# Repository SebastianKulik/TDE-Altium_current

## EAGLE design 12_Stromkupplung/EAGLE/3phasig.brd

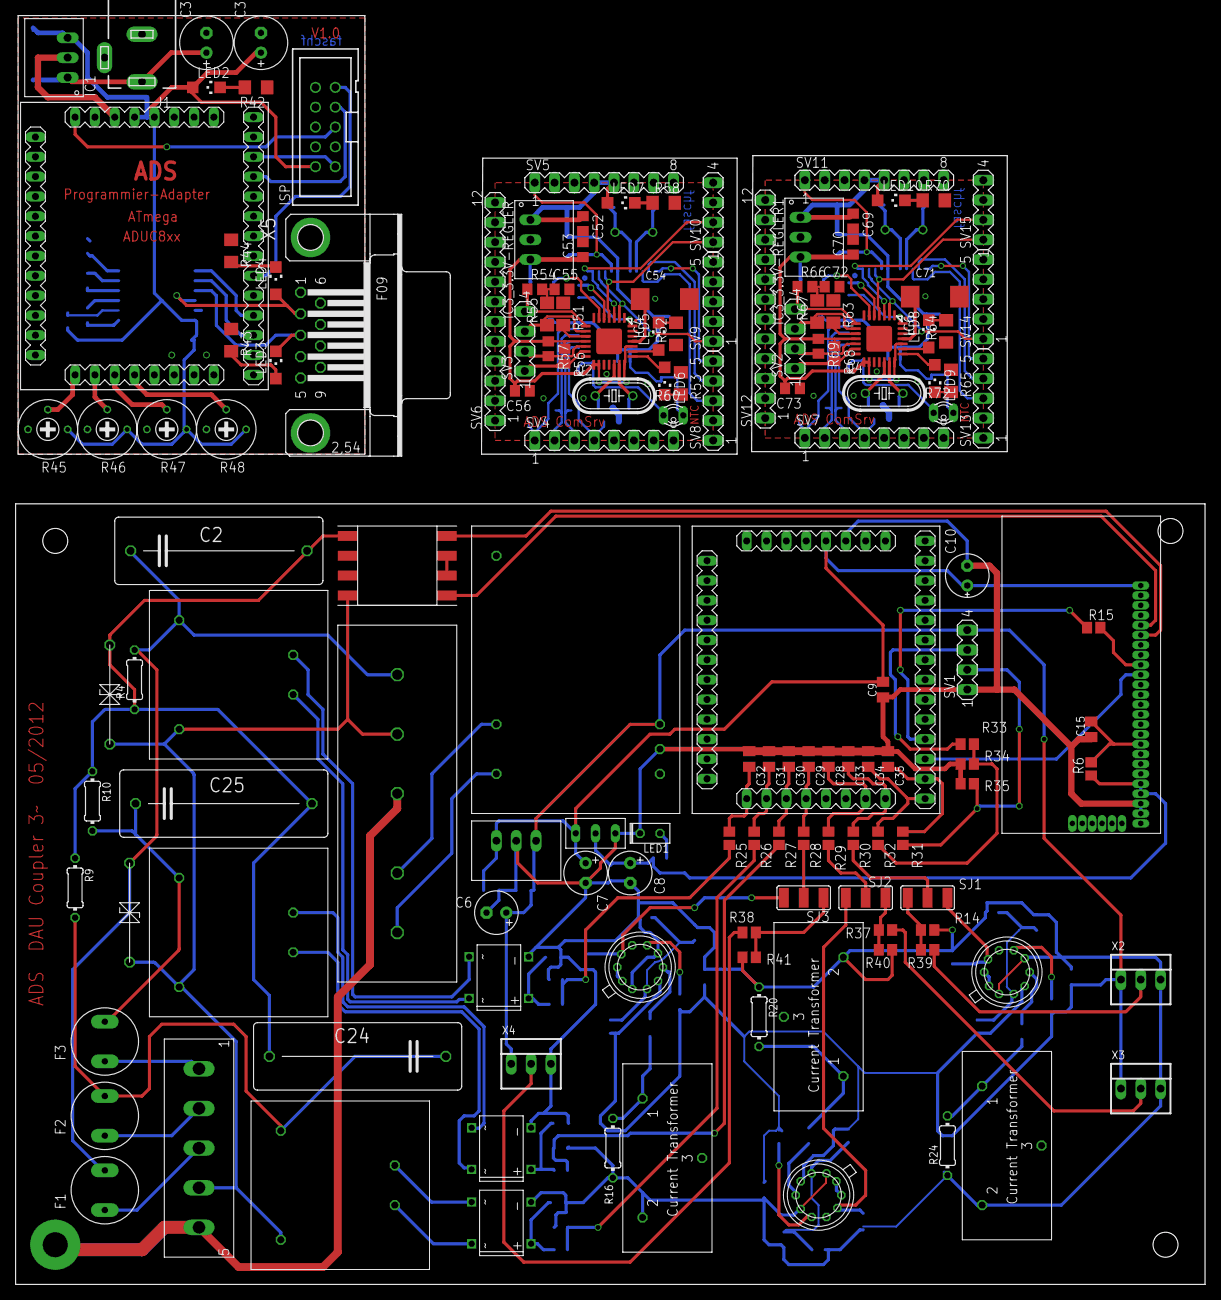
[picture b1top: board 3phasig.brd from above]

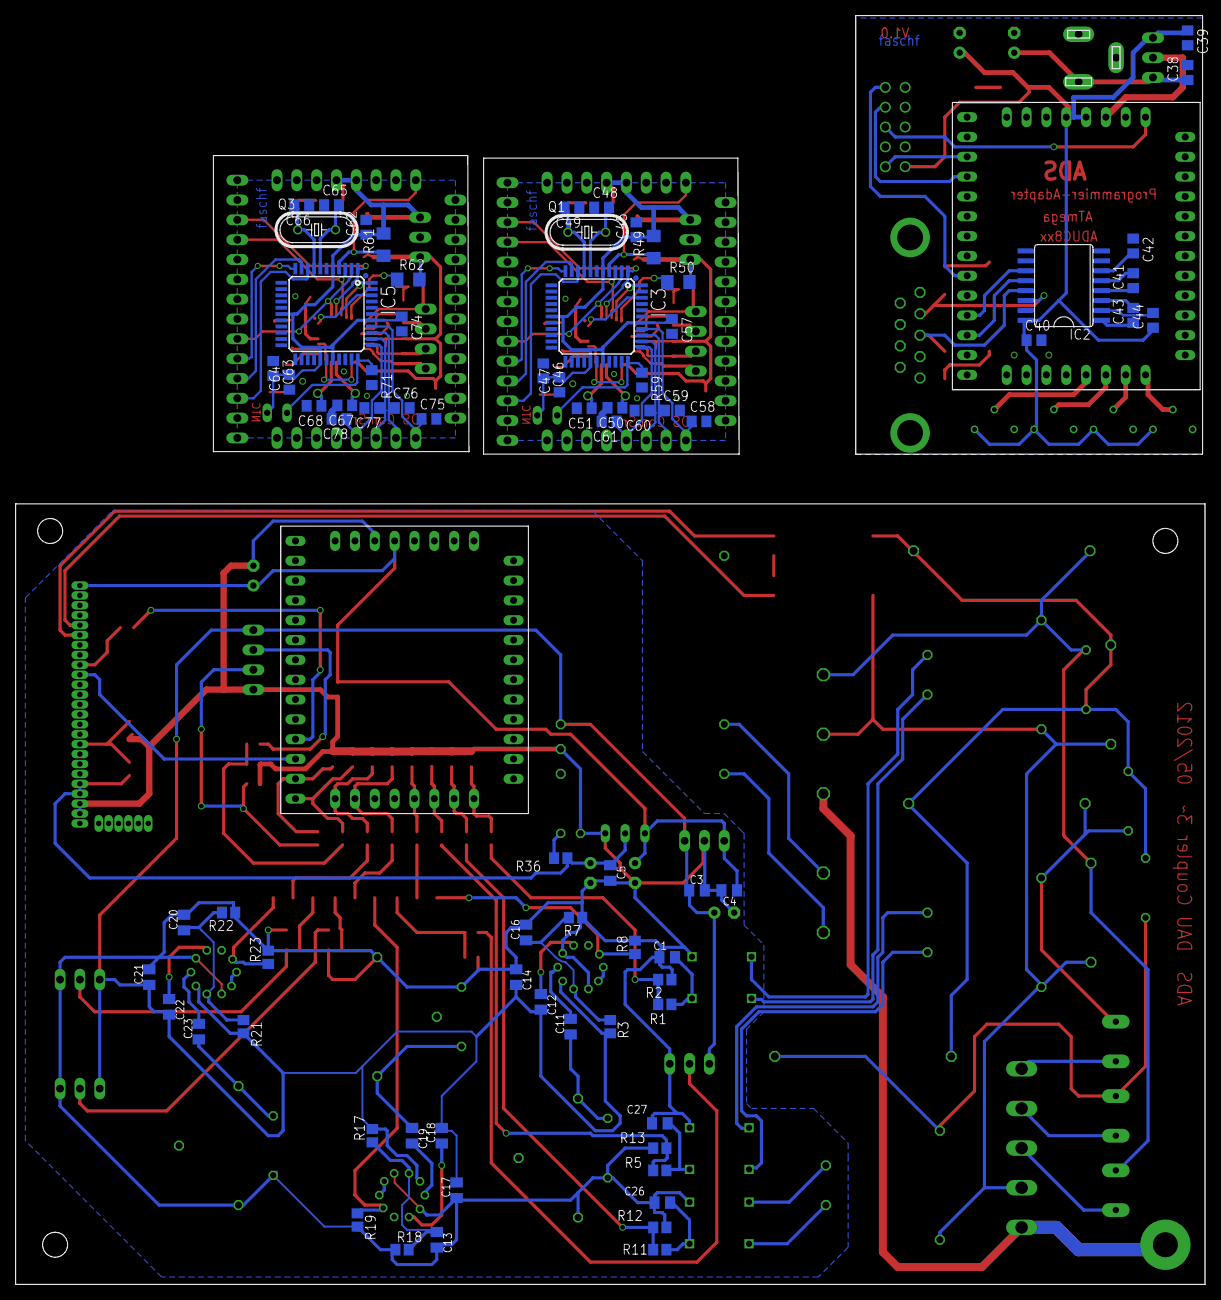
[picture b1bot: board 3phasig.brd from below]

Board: 2 copper layers, 152.4 x 162.5 mm, 222 parts (76 on the bottom side), 165 nets.

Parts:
AC1002_1: AC1010
C1, C11, C13, C14, C15, C16, C17, C19, C20, C21, C23, C26, C27: 1µ; C0805K
C2, C24, C25: 470n/270V; C225-087X268
C3, C4, C5, C9, C28, C29, C30, C31, C32, C33, C34, C35: 100n; C0805K
C6, C7, C8: 4,7µ; E2,5-6
C10: 4µ7; E2,5-6E
C12, C18, C22: 4µ7; C0805K
C36, C37: 10u; E2,5-7
C38, C39, C40, C41, C42, C43, C44, C45, C46, C47, C52, C53, C57, C62, C63, C64, C69, C70, C74: 100n; C0805
C48, C49, C50, C51, C65, C66, C67, C68: 22p; C0805
C54, C71: 10u; SMC_D
C55, C56, C58, C59, C60, C61, C72, C73, C75, C76, C77, C78: 10n; C0805
F1, F2, F3: T250mA/240V; TR5
IC1, IC3_3.3V-REGLER, IC3_3.3V-REGLER1: 78RECOM; RECOM_3POL
IC2: MAX3232CWE; SO16L
IC3, IC5: MEGA32-A; TQFP44
IC4, IC6: ENC28J60QFN28_LONG_28; QFN28_LONG_ERRLES
ISP: 2510-; PAK100/2500-10
J1: DCJ0202
LED1: LED2X5
LED2, LED3, LED4, LED5, LED6, LED7, LED8, LED9, LED10: CHIPLED_1206
P6KE300CA: P6KE300CA; TSV
Q1, Q3: 16MHz; HC49/S
Q2, Q4: 25MHz; HC49/S
R1, R5, R11: 82k; R0805
R2, R12, R13: 33k; R0805
R3, R17, R21: 22k; R0805
R4, R9, R10: 470k; 0204/7
R6: 1M; R0805
R7, R18, R22, R59, R71: 10k; R0805
R8, R19, R23: 4k7; R0805
R14, R40, R41: 220R/33k; R0805
R15, R36: 330R; R0805
R16, R20, R24: 68R; 0204/7
R25, R26, R27, R28, R29, R30, R31, R32: 10R; R0805
R33: 680k; R0805
R34: 470k; R0805
R35: 220R; R0805
R37, R38, R39: 0/82k; R0805
R42, R52, R53, R58, R64, R65, R70: 220R; R1206
R43, R44: 1k2; R1206
R45, R46, R47, R48: 100k; RTRIM3339P
R49, R50, R61, R62: 10k; R1206
R51, R63: 2k2; R1206
R54, R56, R57, R66, R68, R69: 51R; R0805
R55, R67: 51R; R1206
R60, R72: P640
SJ1, SJ2, SJ3: SJ_2W
SV1, SV2, SV3, SV10, SV15: MA04-1
SV4, SV5, SV7, SV11: MA08-1
SV6, SV12: MA12-1
SV8, SV9, SV13, SV14: MA05-1
TSV2: TSV
U$1: RECOM_RAC04_12SA; RAC04_12SA
U$2, U$16, U$18: SICHERHEITSTRAFO; TRAFO_0,35VA
U$3: ADUC831_MINIMUM; ADUC_MINIMUM
U$4: MODEMSTECKER; MODEM_FUSS
U$5: PLC_UEBERTRAGER_V2; PLC-UEBERTRAGER_V2
U$6: MEGA32_COMSERVER; ADUC_MINIMUM
U$7, U$14: AC1010
U$8, U$17, U$19: RECTIFIER
U$10: RECOM_785_05; RECOM785X
U$11: TS1084_HOCH
U$12, U$13, U$15: AD536; TO100_10PIN
U$20: NETZFILTER_05_A; NETZFILTER
X1: CONNECTO_5_POL; CONNECTOR_5_POL
X2, X3, X4: 22-23-2031
X5: F09HP

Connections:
1_TD+: IC4.13, R56.2, SV3.1
1_TD+1: IC6.13, R68.2, SV2.1
2_TD-: IC4.12, R57.2, SV3.2
2_TD-1: IC6.12, R69.2, SV2.2
3_RD+: IC4.9, R55.1, SV3.3
3_RD+1: IC6.9, R67.1, SV2.3
6_RD-: IC4.8, R54.1, SV3.4
6_RD-1: IC6.8, R66.1, SV2.4
+3V3: C5.1, C8.+, R6.1, R36.1, U$4.P$4, U$4.P$5, U$11.OUT
+5V: C4.1, C7.+, C9.2, C10.+, U$3.VCC, U$4.P$25, U$10.VOUT, U$11.IN
+12V: C3.1, C6.+, C12.2, C14.2, C17.2, C18.2, C21.1, C22.2, R3.2, R17.2, R21.2, SV1.4, U$1.+VO, U$10.VIN, U$12.3, U$13.3, U$15.3, X2.1, X3.1, X4.1
ADC0: C32.1, R25.2, U$3.ADC0
ADC1: C31.1, R26.2, U$3.ADC1
ADC2: C30.1, R27.2, U$3.ADC2
ADC3: C29.1, R28.2, U$3.ADC3
ADC4: C28.1, R29.2, U$3.ADC4
ADC5: C33.1, R30.2, U$3.ADC5
ADC6: C58.1, IC3.37, SV4.1
ADC7: C59.1, IC3.36, SV4.2
ADC8: C60.1, IC3.35, SV4.3
ADC9: C61.1, IC3.34, SV4.4
ADC10: C75.1, IC5.37, SV7.1
ADC11: C76.1, IC5.36, SV7.2
ADC12: C77.1, IC5.35, SV7.3
ADC13: C78.1, IC5.34, SV7.4
GND: AC1002_1.P$2, C1.2, C3.2, C4.2, C5.2, C6.-, C7.-, C8.-, C9.1, C10.-, C13.2, C14.1, C15.1, C16.2, C17.1, C20.2, C21.2, C26.2, C27.2, C28.2, C29.2, C30.2, C31.2, C32.2, C33.2, C34.2, C35.2, LED1.K, R2.1, R7.1, R8.2, R12.1, R13.1, R14.1, R16.1, R18.1, R19.2, R20.1, R22.1, R23.2, R24.1, R34.1, R35.1, R40.1, R41.1, SV1.1, U$1.GND, U$3.GND, U$4.P$2, U$4.P$3, U$7.P$2, U$8.-, U$10.GND, U$11.GND, U$12.1, U$12.5, U$13.1, U$13.5, U$14.P$2, U$15.1, U$15.5, U$17.-, U$19.-, X2.3, X3.3, X4.3
GND1: C36.-, C37.-, C38.2, C39.2, C40.2, C42.1, IC1.2, IC2.8, IC2.10, IC2.15, ISP.6, ISP.10, J1.2, J1.3, R42.1, R43.1, R44.1, R45.3, R46.3, R47.3, R48.3, U$6.GND, U$6.GND2, U$6.GND3, X5.5
GND2: C45.2, C46.1, C47.1, C48.1, C49.1, C50.2, C51.2, C52.2, C53.2, C54.-, C55.2, C56.1, C57.2, C58.2, C59.2, C60.2, C61.2, IC3.6, IC3.18, IC3.28, IC3.30, IC3.31, IC3.32, IC3.39, IC3_3.3V-REGLER.2, IC4.7, IC4.14, IC4.17, IC4.18, IC4.26, R51.1, R52.1, R53.1, R58.2, R59.2, SV5.2, SV5.3, SV5.6
GND3: C62.2, C63.1, C64.1, C65.1, C66.1, C67.2, C68.2, C69.2, C70.2, C71.-, C72.2, C73.1, C74.2, C75.2, C76.2, C77.2, C78.2, IC3_3.3V-REGLER1.2, IC5.6, IC5.18, IC5.28, IC5.30, IC5.31, IC5.32, IC5.39, IC6.7, IC6.14, IC6.17, IC6.18, IC6.26, R63.1, R64.1, R65.1, R70.2, R71.2, SV11.2, SV11.3, SV11.6
I1: R28.1, SJ3.2
I1INTERN: R8.1, SJ3.3, U$13.8
I2: R29.1, SJ2.2
I2INTERN: R19.1, SJ2.3, U$12.8
I3: R30.1, SJ1.2
I3INTERN: R23.1, SJ1.3, U$15.8
INT0: IC3.11, SV8.5
INT1: IC5.11, SV13.5
L1: C2.1, F1.2, P6KE300CA.P$1, R4.2, U$2.L, U$20.L
L2: C24.1, F2.2, R9.2, U$16.L
L3: C25.1, F3.2, R10.2, U$18.L
MISO: IC3.2, IC4.2, SV9.1
MISO1: IC5.2, IC6.2, SV14.1
MOSI: IC3.1, IC4.3, SV10.2
MOSI1: IC5.1, IC6.3, SV15.2
N: P6KE300CA.P$2, TSV2.P$2, U$2.N, U$5.8N, U$16.N, U$18.N, U$20.N, X1.P$4
unnamed: R15.2, U$4.P$17
unnamed: AC1002_1.P$1, C11.1, R16.2
unnamed: C11.2, U$13.4
unnamed: U$2.OUT1, U$8.~1
unnamed: U$4.P$20, U$5.1LINE1
unnamed: U$13.9, U$13.10
unnamed: C1.1, R1.2, U$8.+
unnamed: C35.1, R31.2, U$3.ADC7
unnamed: U$2.OUT2, U$8.~2
unnamed: C26.1, R11.2, U$17.+
unnamed: U$16.OUT1, U$17.~1
unnamed: U$16.OUT2, U$17.~2
unnamed: U$4.P$21, U$5.4LINE2
unnamed: R15.1, U$3.TXD
unnamed: U$3.RXD, U$4.P$16
unnamed: U$1.L, U$20.L'
unnamed: C16.1, R3.1, R7.2, U$13.2
unnamed: C36.+, C38.1, IC1.1, J1.1
unnamed: LED1.A, R36.2
unnamed: C15.2, R6.2, U$4.P$9
unnamed: C12.1, U$13.6
unnamed: C19.1, R20.2, U$7.P$1
unnamed: C19.2, U$12.4
unnamed: U$12.9, U$12.10
unnamed: C34.1, R32.2, U$3.ADC6
unnamed: C2.2, C24.2, C25.2, R4.1, R9.1, R10.1, TSV2.P$1, U$5.L5
unnamed: C13.1, R17.1, R18.2, U$12.2
unnamed: ISP.1, U$6.MOSI
unnamed: C18.1, U$12.6
unnamed: C23.1, R24.2, U$14.P$1
unnamed: C23.2, U$15.4
unnamed: U$15.9, U$15.10
unnamed: U$5.2, U$5.3
unnamed: C27.1, R5.2, U$19.+
unnamed: U$18.OUT1, U$19.~1
unnamed: U$18.OUT2, U$19.~2
unnamed: R33.2, SV1.3
unnamed: C20.1, R21.1, R22.2, U$15.2
unnamed: ISP.5, U$6.P24
unnamed: C22.1, U$15.6
unnamed: U$1.N, U$20.N'
unnamed: R37.2, R40.2, SJ2.1
unnamed: R37.1, X3.2
unnamed: R14.2, R39.2, SJ1.1
unnamed: F1.1, X1.P$3
unnamed: F2.1, X1.P$2
unnamed: F3.1, X1.P$1
unnamed: R32.1, R33.1, R34.2
unnamed: R31.1, R35.2, SV1.2
unnamed: R39.1, X2.2
unnamed: R38.2, R41.2, SJ3.1
unnamed: R38.1, X4.2
unnamed: ISP.7, U$6.SCLOCK
unnamed: ISP.9, U$6.MISO
unnamed: IC2.12, U$6.RXD
unnamed: IC2.11, U$6.TXD
unnamed: C44.2, IC2.2
unnamed: C42.2, IC2.6
unnamed: C43.1, IC2.1
unnamed: C43.2, IC2.3
unnamed: C41.1, IC2.4
unnamed: C41.2, IC2.5
unnamed: IC2.14, LED4.A, X5.2
unnamed: LED2.C, R42.2
unnamed: IC2.13, LED3.C, X5.3
unnamed: LED3.A, R43.2
unnamed: LED4.C, R44.2
unnamed: R45.2, U$6.ADC0
unnamed: R46.2, U$6.ADC1
unnamed: R47.2, U$6.ADC2
unnamed: R48.2, U$6.ADC3
unnamed: C49.2, IC3.8, Q1.1
unnamed: C48.2, IC3.7, Q1.2
unnamed: C50.1, IC4.19, Q2.1
unnamed: C51.1, IC4.20, Q2.2
unnamed: C54.+, IC4.25
unnamed: IC3.42, IC4.28
unnamed: IC4.6, R50.1
unnamed: IC4.10, R51.2
unnamed: LED5.C, R52.2
unnamed: IC4.23, LED5.A
unnamed: IC4.22, LED6.A
unnamed: LED6.C, R53.2
unnamed: C55.1, R54.2, R55.2
unnamed: LED7.C, R58.1
unnamed: IC3.33, R59.1, R60.1
unnamed: C66.2, IC5.8, Q3.1
unnamed: C65.2, IC5.7, Q3.2
unnamed: C67.1, IC6.19, Q4.1
unnamed: C68.1, IC6.20, Q4.2
unnamed: C71.+, IC6.25
unnamed: IC5.42, IC6.28
unnamed: IC6.6, R62.1
unnamed: IC6.10, R63.2
unnamed: LED8.C, R64.2
unnamed: IC6.23, LED8.A
unnamed: IC6.22, LED9.A
unnamed: LED9.C, R65.2
unnamed: C72.1, R66.2, R67.2
unnamed: LED10.C, R70.1
unnamed: IC5.33, R71.1, R72.1
PE: U$20.PE, X1.P$5
RESET: IC3.4, R49.1, SV5.1
RESET1: IC5.4, R61.1, SV11.1
RXD: IC3.9, SV8.3
RXD1: IC5.9, SV13.3
SCK: IC3.3, IC4.4, SV10.1
SCK1: IC5.3, IC6.4, SV15.1
SS: IC3.44, IC4.5
SS1: IC5.44, IC6.5
TXD: IC3.10, SV8.4
TXD1: IC5.10, SV13.4
U1: R1.1, R2.2, R25.1
U2: R11.1, R12.2, R26.1
U3: R5.1, R13.2, R27.1
VCC: C37.+, C39.1, C40.1, C44.1, IC1.3, IC2.16, ISP.2, LED2.A, R45.1, R46.1, R47.1, R48.1, U$6.VCC, U$6.VCC1
VCC_3V: C53.1, C56.2, IC3_3.3V-REGLER.3, IC4.11, IC4.15, IC4.16, IC4.21, IC4.24, R50.2, R56.1, R57.1
VCC_3V1: C70.1, C73.2, IC3_3.3V-REGLER1.3, IC6.11, IC6.15, IC6.16, IC6.21, IC6.24, R62.2, R68.1, R69.1
VCC_5V: C45.1, C46.2, C47.2, C52.1, C57.1, IC3.5, IC3.17, IC3.27, IC3.29, IC3.38, IC3_3.3V-REGLER.1, LED7.A, R49.2, R60.2, SV5.4, SV5.5
VCC_5V1: C62.1, C63.2, C64.2, C69.1, C74.1, IC3_3.3V-REGLER1.1, IC5.5, IC5.17, IC5.27, IC5.29, IC5.38, LED10.A, R61.2, R72.2, SV11.4, SV11.5

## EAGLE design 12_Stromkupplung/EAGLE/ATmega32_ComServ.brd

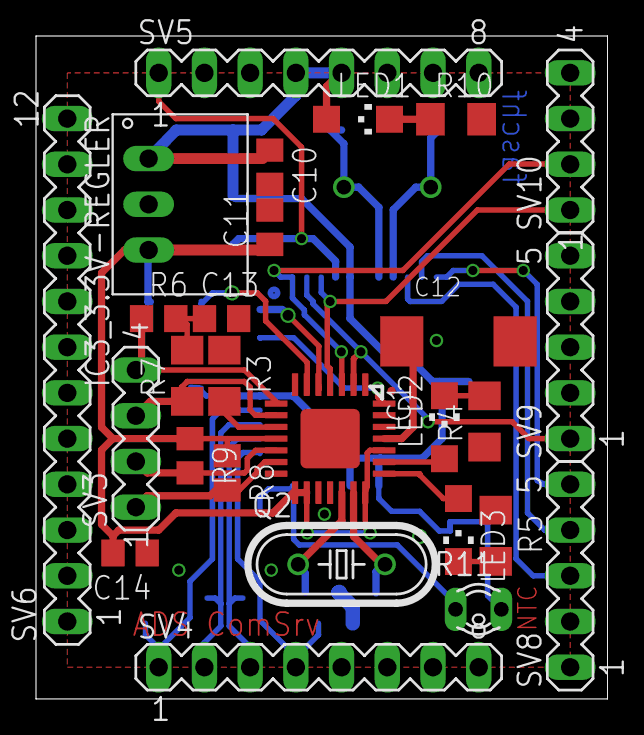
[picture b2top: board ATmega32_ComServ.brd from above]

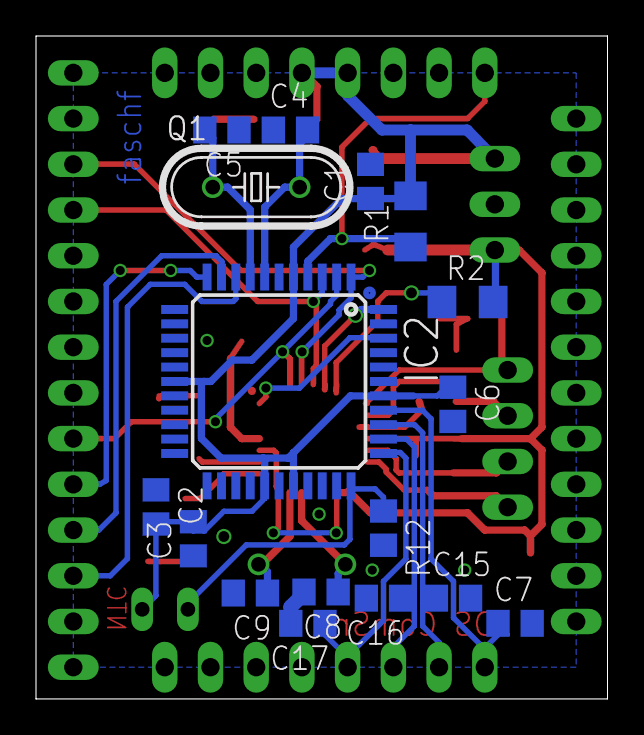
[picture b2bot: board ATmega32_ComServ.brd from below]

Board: 2 copper layers, 31.8 x 36.8 mm, 44 parts (17 on the bottom side), 34 nets.

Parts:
C1, C2, C3, C6, C10, C11: 100n; C0805
C4, C5, C8, C9: 22p; C0805
C7, C13, C14, C15, C16, C17: 10n; C0805
C12: 10u; SMC_D
IC1: ENC28J60QFN28_LONG_28; QFN28_LONG_ERRLES
IC2: MEGA32-A; TQFP44
IC3_3.3V-REGLER: 78RECOM; RECOM_3POL
LED1, LED2, LED3: CHIPLED_1206
Q1: 16MHz; HC49/S
Q2: 25MHz; HC49/S
R1, R2: 10k; R1206
R3: 2k2; R1206
R4, R5, R10: 220R; R1206
R6, R8, R9: 51R; R0805
R7: 51R; R1206
R11: P640
R12: 10k; R0805
SV3, SV10: MA04-1
SV4, SV5: MA08-1
SV6: MA12-1
SV8, SV9: MA05-1

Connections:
1_TD+: IC1.13, R8.2, SV3.1
2_TD-: IC1.12, R9.2, SV3.2
3_RD+: IC1.9, R7.1, SV3.3
6_RD-: IC1.8, R6.1, SV3.4
ADC0: C7.1, IC2.37, SV4.1
ADC1: C15.1, IC2.36, SV4.2
ADC2: C16.1, IC2.35, SV4.3
ADC3: C17.1, IC2.34, SV4.4
GND: C1.2, C2.1, C3.1, C4.1, C5.1, C6.2, C7.2, C8.2, C9.2, C10.2, C11.2, C12.-, C13.2, C14.1, C15.2, C16.2, C17.2, IC1.7, IC1.14, IC1.17, IC1.18, IC1.26, IC2.6, IC2.18, IC2.28, IC2.30, IC2.31, IC2.32, IC2.39, IC3_3.3V-REGLER.2, R3.1, R4.1, R5.1, R10.2, R12.2, SV5.2, SV5.3, SV5.6
INT0: IC2.11, SV8.5
MISO: IC1.2, IC2.2, SV9.1
MOSI: IC1.3, IC2.1, SV10.2
unnamed: C5.2, IC2.8, Q1.1
unnamed: C4.2, IC2.7, Q1.2
unnamed: LED1.C, R10.1
unnamed: C8.1, IC1.19, Q2.1
unnamed: C9.1, IC1.20, Q2.2
unnamed: C12.+, IC1.25
unnamed: IC2.33, R11.1, R12.1
unnamed: IC1.28, IC2.42
unnamed: IC1.6, R2.1
unnamed: IC1.10, R3.2
unnamed: LED2.C, R4.2
unnamed: IC1.23, LED2.A
unnamed: IC1.22, LED3.A
unnamed: LED3.C, R5.2
unnamed: C13.1, R6.2, R7.2
RESET: IC2.4, R1.1, SV5.1
RXD: IC2.9, SV8.3
SCK: IC1.4, IC2.3, SV10.1
SS: IC1.5, IC2.44
TXD: IC2.10, SV8.4
VCC_3V: C11.1, C14.2, IC1.11, IC1.15, IC1.16, IC1.21, IC1.24, IC3_3.3V-REGLER.3, R2.2, R8.1, R9.1
VCC_5V: C1.1, C2.2, C3.2, C6.1, C10.1, IC2.5, IC2.17, IC2.27, IC2.29, IC2.38, IC3_3.3V-REGLER.1, LED1.A, R1.2, R11.2, SV5.4, SV5.5

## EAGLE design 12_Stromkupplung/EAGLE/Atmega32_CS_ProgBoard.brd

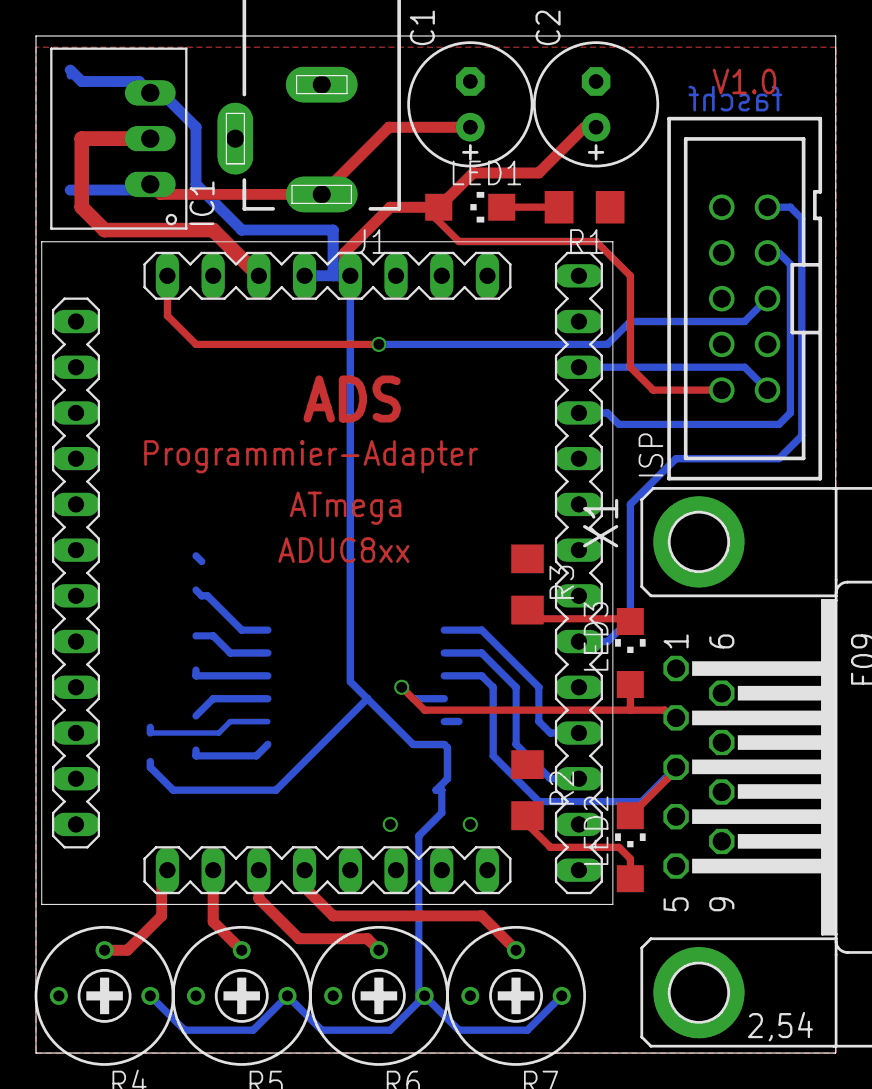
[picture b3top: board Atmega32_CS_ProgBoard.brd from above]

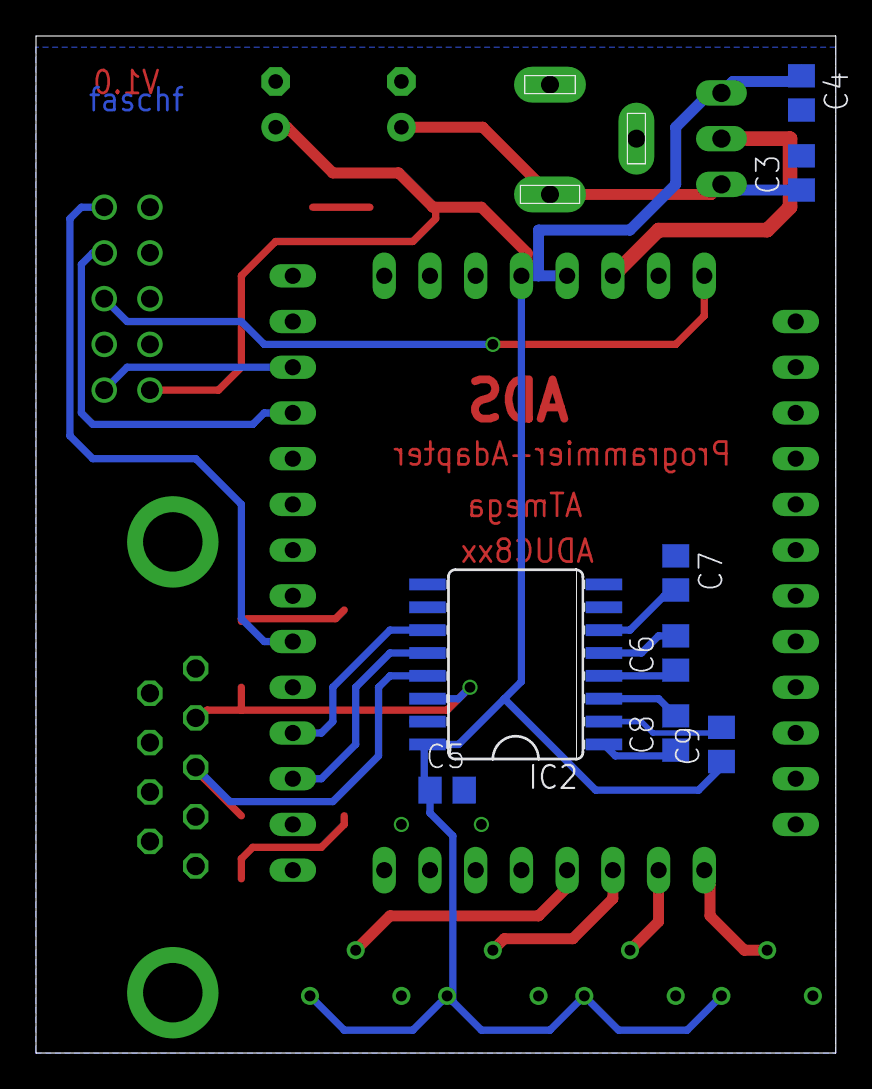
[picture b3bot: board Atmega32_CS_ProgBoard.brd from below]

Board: 2 copper layers, 44.4 x 56.5 mm, 25 parts (8 on the bottom side), 24 nets.

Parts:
C1, C2: 10u; E2,5-7
C3, C4, C5, C6, C7, C8, C9: 100n; C0805
IC1: 78RECOM; RECOM_3POL
IC2: MAX3232CWE; SO16L
ISP: 2510-; PAK100/2500-10
J1: DCJ0202
LED1, LED2, LED3: CHIPLED_1206
R1: 220R; R1206
R2, R3: 1k2; R1206
R4, R5, R6, R7: 100k; RTRIM3339P
U$1: MEGA32_COMSERVER; ADUC_MINIMUM
X1: F09HP

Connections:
GND: C1.-, C2.-, C3.2, C4.2, C5.2, C7.1, IC1.2, IC2.8, IC2.10, IC2.15, ISP.6, ISP.10, J1.2, J1.3, R1.1, R2.1, R3.1, R4.3, R5.3, R6.3, R7.3, U$1.GND, U$1.GND2, U$1.GND3, X1.5
unnamed: ISP.7, U$1.SCLOCK
unnamed: C1.+, C3.1, IC1.1, J1.1
unnamed: ISP.9, U$1.MISO
unnamed: ISP.1, U$1.MOSI
unnamed: ISP.5, U$1.P24
unnamed: IC2.12, U$1.RXD
unnamed: IC2.11, U$1.TXD
unnamed: C9.2, IC2.2
unnamed: C7.2, IC2.6
unnamed: C8.1, IC2.1
unnamed: C8.2, IC2.3
unnamed: C6.1, IC2.4
unnamed: C6.2, IC2.5
unnamed: IC2.14, LED3.A, X1.2
unnamed: IC2.13, LED2.C, X1.3
unnamed: LED1.C, R1.2
unnamed: LED2.A, R2.2
unnamed: LED3.C, R3.2
unnamed: R4.2, U$1.ADC0
unnamed: R5.2, U$1.ADC1
unnamed: R6.2, U$1.ADC2
unnamed: R7.2, U$1.ADC3
VCC: C2.+, C4.1, C5.1, C9.1, IC1.3, IC2.16, ISP.2, LED1.A, R4.1, R5.1, R6.1, R7.1, U$1.VCC, U$1.VCC1
